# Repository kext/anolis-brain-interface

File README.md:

# Anolis Brain Interface

This repository contains the hardware and software files for the Anolis Brain Interface.

## PCB

The source and production files for the flexible PCB are in the [`pcb`](pcb) directory.
See the [Readme there](pcb/README.md) for instructions to setup your work environment.

## Firmware

The firmware for the brain interface and the dongle is in the [`firmware`](firmware) directory.
There you can find more information how to compile, flash and run the firmware on your device.

## Licence

The source code and PCB design files are dual licenced under the [MIT](LICENCE-MIT) and [Apache 2.0](LICENCE-APACHE) licences.

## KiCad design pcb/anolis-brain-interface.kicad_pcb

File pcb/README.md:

# Anolis Brain Interface PCB

## Setup

To work on the project files you need the KiCad EDA software in version 7.

KiCad can be downloaded from the [KiCad website](https://www.kicad.org/).
Download the version for your operating system and follow the instructions.

## Releases

Released versions can be found in the [`releases`](releases) directory.

## Changelog

All notable changes to the PCB should be listed below.

### [0.1.0] - 2023-11-20
- First version

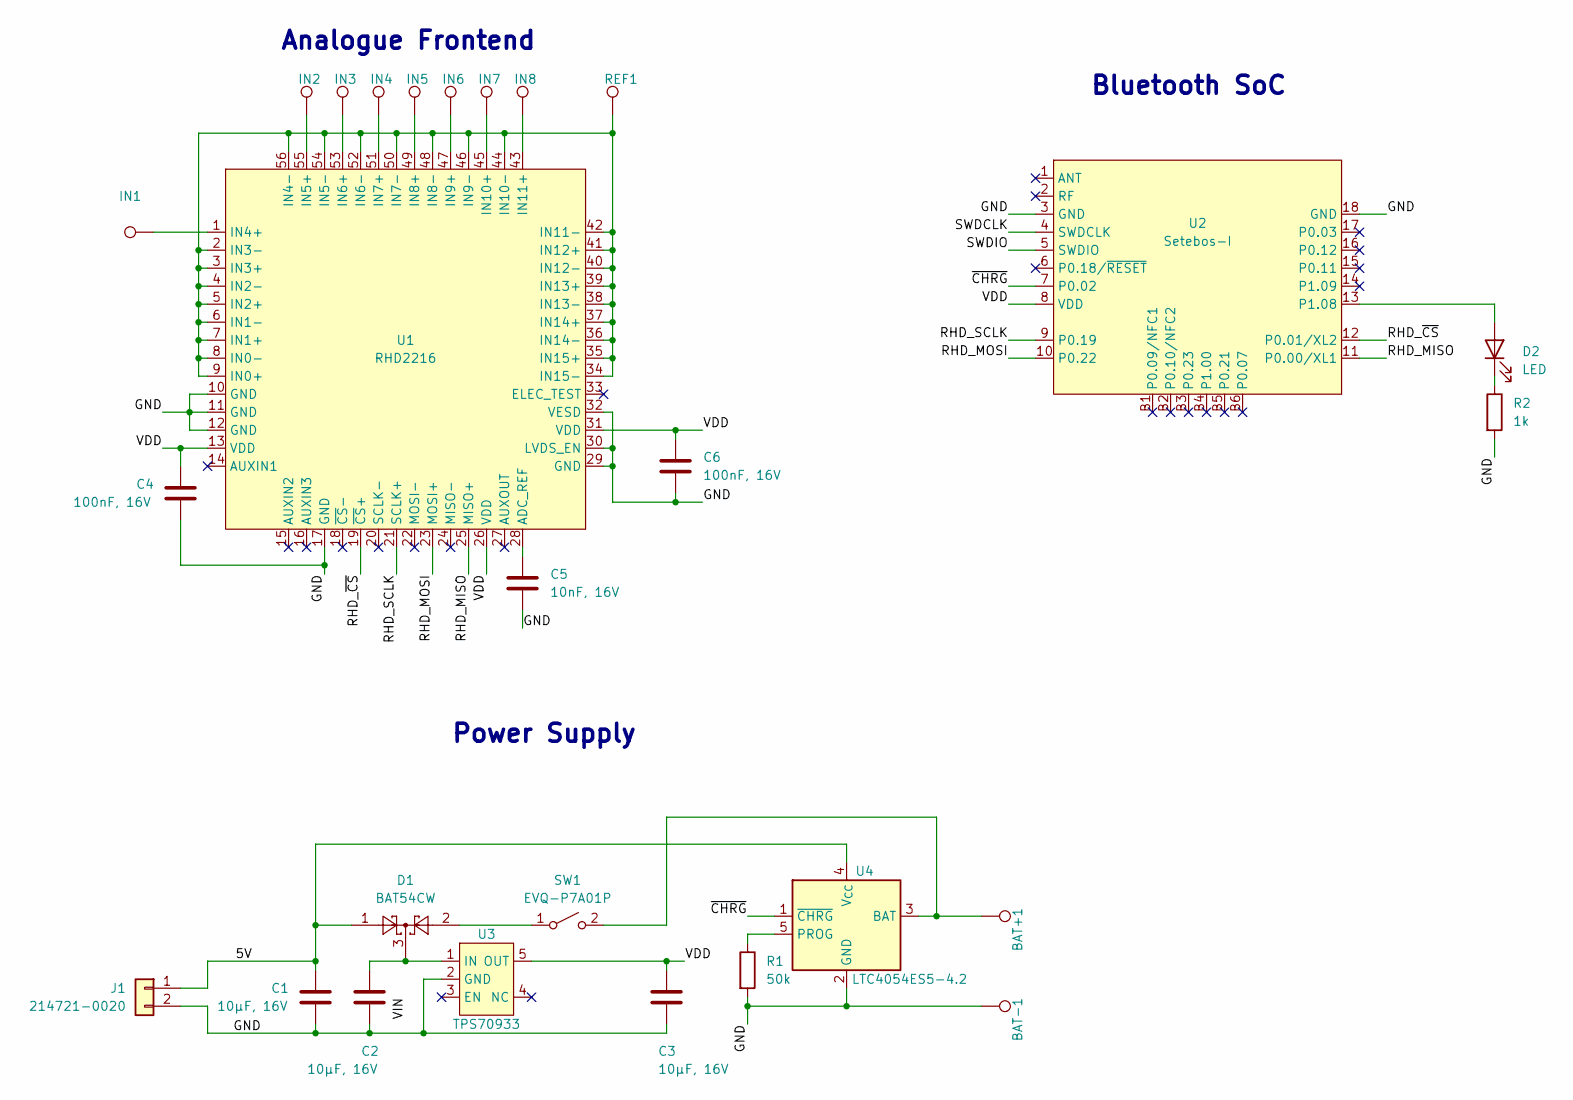
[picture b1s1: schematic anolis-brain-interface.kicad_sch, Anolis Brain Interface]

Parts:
BAT+1: TestPoint; TestPoint_Pad_1.0x1.0mm
BAT-1: TestPoint; TestPoint_Pad_1.0x1.0mm
C1, C2, C3: 10µF, 16V; C_0603_1608Metric
C4, C6: 100nF, 16V; C_0402_1005Metric
C5: 10nF, 16V; C_0402_1005Metric
D1: BAT54CW; SOT-323_SC-70
D2: LED; LED_0402_1005Metric
IN1, IN2, IN3, IN4, IN5, IN6, IN7, IN8: TestPoint; TestPoint_Pad_1.0x1.0mm
J1: 214721-0020
R1: 50k; R_0402_1005Metric
R2: 1k; R_0402_1005Metric
REF1: TestPoint; TestPoint_Pad_1.0x1.0mm
SW1: EVQ-P7A01P; SW_SPST_EVQP7A
U1: RHD2216; QFN-56-EP
U2: Setebos-I; setebos-no-drc
U3: TPS70933; TSOT-23-5
U4: LTC4054ES5-4.2; TSOT-23-5

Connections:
/5V: C1.1, D1.1, J1.1, U4.4 (V_{CC})
/GND: BAT-1.1, C1.2, C2.2, C3.2, C4.2, C5.2, C6.2, J1.2, R1.2, R2.2, U1.10 (GND), U1.11 (GND), U1.12 (GND), U1.17 (GND), U1.29 (GND), U1.30 (LVDS_EN), U1.32 (VESD), U2.3 (GND), U2.18 (GND), U3.2 (GND), U4.2 (GND)
/RHD_MISO: U1.25 (MISO+), U2.11 (P0.00/XL1)
/RHD_MOSI: U1.23 (MOSI+), U2.10 (P0.22)
/RHD_SCLK: U1.21 (SCLK+), U2.9 (P0.19)
/RHD_~CS: U1.19 (~CS+), U2.12 (P0.01/XL2)
/SWDCLK: U2.4 (SWDCLK)
/SWDIO: U2.5 (SWDIO)
/VDD: C3.1, C4.1, C6.1, U1.13 (VDD), U1.26 (VDD), U1.31 (VDD), U2.8 (VDD), U3.5 (OUT)
/~CHRG: U2.7 (P0.02), U4.1 (~CHRG)
unnamed: D2.2 (A), U2.13 (P1.08)
unnamed: D2.1 (K), R2.1
unnamed: D1.2, SW1.1 (A)
unnamed: BAT+1.1, SW1.2 (B), U4.3 (BAT)
unnamed: C5.1, U1.28 (ADC_REF)
unnamed: REF1.1, U1.2 (IN3-), U1.3 (IN3+), U1.4 (IN2-), U1.5 (IN2+), U1.6 (IN1-), U1.7 (IN1+), U1.8 (IN0-), U1.9 (IN0+), U1.34 (IN15-), U1.35 (IN15+), U1.36 (IN14-), U1.37 (IN14+), U1.38 (IN13-), U1.39 (IN13+), U1.40 (IN12-), U1.41 (IN12+), U1.42 (IN11-), U1.44 (IN10-), U1.46 (IN9-), U1.48 (IN8-), U1.50 (IN7-), U1.52 (IN6-), U1.54 (IN5-), U1.56 (IN4-)
unnamed: IN1.1, U1.1 (IN4+)
unnamed: IN2.1, U1.55 (IN5+)
unnamed: IN3.1, U1.53 (IN6+)
unnamed: IN4.1, U1.51 (IN7+)
unnamed: IN5.1, U1.49 (IN8+)
unnamed: IN6.1, U1.47 (IN9+)
unnamed: IN7.1, U1.45 (IN10+)
unnamed: IN8.1, U1.43 (IN11+)
unnamed: C2.1, D1.3, U3.1 (IN)
unnamed: R1.1, U4.5 (PROG)

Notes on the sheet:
Power Supply
Analogue Frontend
Bluetooth SoC

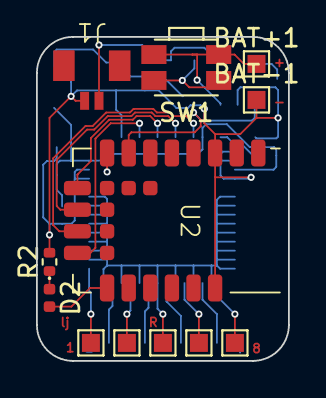
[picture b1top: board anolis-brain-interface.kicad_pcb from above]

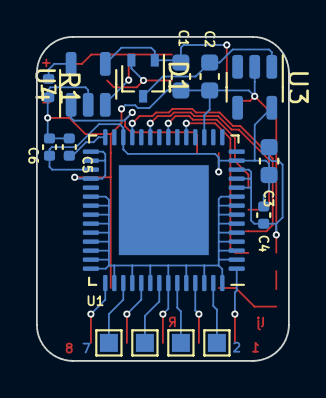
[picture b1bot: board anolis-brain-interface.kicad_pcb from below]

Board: 2 copper layers, 14.0 x 18.0 mm, 27 parts (15 on the bottom side), 24 nets.

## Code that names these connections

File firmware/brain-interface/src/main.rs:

//! Firmware for the Anolis Brain Interface

#![no_std]
#![no_main]
#![feature(type_alias_impl_trait)]

extern crate alloc;

use core::{cell::RefCell, ops::BitAnd};

use data_channel::{BoxPacket, L2capError};
use defmt::{info, unwrap, warn};
use embassy_executor::Spawner;
use embassy_futures::join::join;
use embassy_nrf::{
    bind_interrupts,
    gpio::{AnyPin, Input, Level, Output, OutputDrive, Pull},
    interrupt, peripherals,
    uarte::{self, UarteTx},
};
use embassy_time::Timer;
use embedded_alloc::Heap;
use nrf_softdevice::{
    ble::{
        l2cap::{self, L2cap, Packet, RxError},
        peripheral::{self, ConnectableAdvertisement},
        Phy, TxPower,
    },
    raw, Softdevice,
};

// global logger
use defmt_rtt as _;
// time driver
use embassy_nrf as _;
use panic_probe as _;

mod rhd2216;
use rhd2216::RHD2216;

/// Use the embedded alloc heap to enable [`Vec`](alloc::vec::Vec) and [`BoxPacket`].
#[global_allocator]
static HEAP: Heap = Heap::empty();

bind_interrupts!(struct Irqs {
    TIMER2 => rhd2216::InterruptHandler;
    UARTE1 => uarte::InterruptHandler<peripherals::UARTE1>;
});

/// The Softdevice task. Must be started after enabling the Softdevice.
#[embassy_executor::task]
async fn softdevice_task(sd: &'static Softdevice) -> ! {
    sd.run().await
}

#[embassy_executor::task]
async fn blink_task(led_pin: AnyPin, chrg_pin: AnyPin) -> ! {
    let mut led = Output::new(led_pin, Level::Low, OutputDrive::Standard);
    let chrg_status = Input::new(chrg_pin, Pull::Up);
    loop {
        for i in 0..4 {
            led.set_level(Level::from(i.bitand(1) == 0 || chrg_status.is_high()));
            Timer::after_millis(500).await;
        }
    }
}

/// Advertisement data for the device.
/// Contains the UUID of the brain interface service so the dongle knows to which device to connect.
#[rustfmt::skip]
const ADVERTISEMENT_DATA: &[u8] = &[
    // Flags
    2, 1, raw::BLE_GAP_ADV_FLAGS_LE_ONLY_GENERAL_DISC_MODE as u8,
    // Complete List of 128-bit Service Class UUIDs
    // edb74b42-8347-4285-a102-86f0b64c533c
    17, 7,
    0x3c, 0x53, 0x4c, 0xb6, 0xf0, 0x86, 0x02, 0xa1,
    0x85, 0x42, 0x47, 0x83, 0x42, 0x4b, 0xb7, 0xed,
];

/// Get the [`ConnectableAdvertisement`] for this device.
pub fn advertisement() -> ConnectableAdvertisement<'static> {
    ConnectableAdvertisement::ScannableUndirected {
        adv_data: ADVERTISEMENT_DATA,
        scan_data: &[],
    }
}

/// Alias for the packet type to have one place to change the size.
type MyPacket = BoxPacket<2048>;

/// Shared state between the receiver and sender task.
#[derive(defmt::Format)]
struct State {
    should_stop: bool,
}

/// Start the RHD and keep sending data packets over the L2CAP channel.
async fn send_rhd_data(
    rhd: &mut RHD2216<'_>,
    channel: &l2cap::Channel<MyPacket>,
    state: &RefCell<State>,
) -> Result<(), L2capError<MyPacket>> {
    info!("Starting");
    let mut rhd = rhd.start();
    loop {
        if state.borrow().should_stop {
            return Ok(());
        }
        let d = rhd.read().await;
        let mut packet = MyPacket::new().ok_or(RxError::AllocateFailed)?;
        assert!(MyPacket::MTU / 2 > d.frames.len());
        packet.append(&[(d.sequence_number & 255) as u8, d.channels as u8]);
        for v in &d.frames {
            packet.append(&v.to_le_bytes());
        }
        channel.try_tx(packet).or_else(|e| {
            if let l2cap::TxError::TxQueueFull(_) = e {
                warn!("Packet lost");
                Ok(())
            } else {
                Err(e)
            }
        })?;
    }
}

/// Receive commands and interpret them.
async fn receive_commands(channel: &l2cap::Channel<MyPacket>, state: &RefCell<State>) -> () {
    if let Ok(_) = channel.rx().await {
        state.borrow_mut().should_stop = true;
    }
}

/// The main task.
#[embassy_executor::main]
async fn main(spawner: Spawner) {
    info!("Start");

    // Initialise allocator
    {
        use core::mem::MaybeUninit;
        const HEAP_SIZE: usize = 1024 * 128;
        static mut HEAP_MEM: [MaybeUninit<u8>; HEAP_SIZE] = [MaybeUninit::uninit(); HEAP_SIZE];
        unsafe { HEAP.init(HEAP_MEM.as_ptr() as usize, HEAP_SIZE) }
    }

    // First we get the peripherals access crate.
    let mut config = embassy_nrf::config::Config::default();
    config.gpiote_interrupt_priority = interrupt::Priority::P3;
    config.time_interrupt_priority = interrupt::Priority::P3;
    let p = embassy_nrf::init(config);

    let config = nrf_softdevice::Config {
        clock: Some(raw::nrf_clock_lf_cfg_t {
            source: raw::NRF_CLOCK_LF_SRC_SYNTH as u8,
            rc_ctiv: 0,
            rc_temp_ctiv: 0,
            accuracy: raw::NRF_CLOCK_LF_ACCURACY_500_PPM as u8,
        }),
        conn_gap: Some(raw::ble_gap_conn_cfg_t {
            conn_count: 1,
            event_length: 40,
        }),
        conn_gatt: Some(raw::ble_gatt_conn_cfg_t { att_mtu: 256 }),
        conn_gattc: Some(raw::ble_gattc_conn_cfg_t {
            write_cmd_tx_queue_size: 0,
        }),
        conn_gatts: Some(raw::ble_gatts_conn_cfg_t {
            hvn_tx_queue_size: 0,
        }),
        gatts_attr_tab_size: Some(raw::ble_gatts_cfg_attr_tab_size_t {
            attr_tab_size: 1024,
        }),
        gap_role_count: Some(raw::ble_gap_cfg_role_count_t {
            adv_set_count: 1,
            periph_role_count: 1,
            central_role_count: 1,
            central_sec_count: 0,
            _bitfield_1: raw::ble_gap_cfg_role_count_t::new_bitfield_1(0),
        }),
        gap_device_name: Some(raw::ble_gap_cfg_device_name_t {
            p_value: b"Brain Interface" as *const u8 as _,
            current_len: 15,
            max_len: 15,
            write_perm: raw::ble_gap_conn_sec_mode_t {
                _bitfield_1: raw::ble_gap_conn_sec_mode_t::new_bitfield_1(1, 1),
            },
            _bitfield_1: raw::ble_gap_cfg_device_name_t::new_bitfield_1(
                raw::BLE_GATTS_VLOC_STACK as u8,
            ),
        }),
        conn_l2cap: Some(raw::ble_l2cap_conn_cfg_t {
            ch_count: 1,
            rx_mps: 256,
            tx_mps: 256,
            rx_queue_size: 3,
            tx_queue_size: data_channel::QUEUE_SIZE,
        }),
        ..Default::default()
    };

    // Pin definitions
    let _b1: AnyPin = p.P0_09.into();
    let _b2: AnyPin = p.P0_10.into();
    let _b3: AnyPin = p.P0_23.into();
    let _b4: AnyPin = p.P1_00.into();
    let _b5: AnyPin = p.P0_21.into();
    let _b6: AnyPin = p.P0_07.into();

    let _chrg: AnyPin = p.P0_02.into();

    let _led: AnyPin = p.P1_08.into();

    let _rhd_cs: AnyPin = p.P0_01.into();
    let _rhd_clk: AnyPin = p.P0_19.into();
    let _rhd_mosi: AnyPin = p.P0_22.into();
    let _rhd_miso: AnyPin = p.P0_00.into();

    let sd = Softdevice::enable(&config);
    let l2cap = L2cap::init(sd);

    unwrap!(spawner.spawn(softdevice_task(sd)));
    unwrap!(spawner.spawn(blink_task(_led, _chrg)));

    // Enable UARTE, otherwise SPI3 will not work.
    let mut uart = UarteTx::new(p.UARTE1, Irqs, _b1, Default::default());
    let _ = uart.write(&[1, 2, 3]).await;

    let mut rhd = RHD2216::new(
        Irqs,
        p.SPI3,
        p.TIMER1,
        p.TIMER2,
        p.PPI_CH0.into(),
        p.PPI_CH1.into(),
        _rhd_cs,
        _rhd_clk,
        _rhd_mosi,
        _rhd_miso,
    );

    loop {
        info!("Waiting for connection");
        let config = peripheral::Config {
            tx_power: TxPower::Plus8dBm,
            secondary_phy: Phy::M2,
            interval: 160,
            ..Default::default()
        };

        if let Ok(connection) =
            peripheral::advertise_connectable(sd, advertisement(), &config).await
        {
            info!("advertising done! I have a connection.");
            let config = nrf_softdevice::ble::l2cap::Config { credits: 3 };
            let channel = l2cap.listen(&connection, &config, data_channel::PSM).await;
            if let Ok(channel) = channel {
                let state = RefCell::new(State { should_stop: false });
                let _result = join(
                    send_rhd_data(&mut rhd, &channel, &state),
                    receive_commands(&channel, &state),
                )
                .await;
                info!("{}", _result);
            }
        }
        Timer::after_millis(1000).await;
    }
}

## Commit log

2023-10-17 First commit.
2023-10-17 Added links.
2023-10-17 Started work on PCB.
2023-10-17 Added uSD socket.
2023-10-18 Added power supply.
2023-10-18 Added capacitors.
2023-10-18 Added attachment slits.
2023-10-18 Created doc folder and list of questions.
2023-10-18 Changed board material to polyimide.
2023-10-18 Added battery connector.
2023-10-19 Added question about lizard species.
2023-10-19 Diode added.
2023-10-25 First draft for the firmware.
2023-10-25 Documentation for the RHD2216.
2023-10-25 Settings for Rust Analyzer.
2023-10-25 Fill the TX buffer with the correct commands.
2023-10-25 Don't forget the samples in the first overflow.
2023-10-26 Enable debug info for release mode.
2023-10-26 RHD works.
2023-10-27 Implemented BLE liveview.
2023-10-27 Throughput calculations.
2023-10-27 Added words for spell checker.
2023-10-27 Answers.
2023-10-27 Tuned parameters.
2023-10-27 Questions updated.
2023-10-30 Improved code.
2023-10-30 Segmented draft.
2023-11-01 Improved formatting.
2023-11-01 Clippy improvements.
2023-11-01 Added counter.
2023-11-03 Created a Cargo workspace for the firmware.
2023-11-03 More words for the spell checker.
2023-11-03 Power supply documentation.
2023-11-03 Removed dependencies.
2023-11-05 Created BLE Service library.
2023-11-06 Dongle WIP.
2023-11-06 Rewrote transport layer using L2CAP.
2023-11-08 Implemented browser display with WebUSB.
2023-11-08 Updated dependencies.
2023-11-09 Report 2023-11-09.
2023-11-09 We need to start UARTE at the beginning or SPI will not work.
2023-11-10 Measured power consumption.
2023-11-10 Added SKIP_CHANNELS.
2023-11-10 A picture of the estimated board dimensions.
2023-11-11 Implemented Clippy suggestions.
2023-11-14 Made allocation failure for packet explicit.
2023-11-14 More documentation.
2023-11-14 Better names.
2023-11-14 Measured component weights.
2023-11-15 Better docs.
2023-11-15 Stray backtick.
2023-11-17 New PCB design.
2023-11-18 Implemented a run token for RHD.
2023-11-20 PCB done.
2023-11-20 Improved routing.
2023-11-20 PCB version 0.1.0.
2023-11-20 Order number corrected.
2023-11-20 Fixed inconsistent routing.
2023-11-21 Include sequence counter in the RHD module.
2023-11-21 Less confusing terminology.
2023-11-28 Replaced incorrect order number.
2023-12-01 Fixed reconnection problems and improved interface.
2023-12-01 Better plots.
2023-12-05 Automatically format rust files.
2023-12-07 Adapted the code for the final hardware.
2023-12-08 Unified data and command channels.
2023-12-08 Licences.
2023-12-08 Added instructions for flashing the softdevice.
2023-12-14 Made connection more stable.
2023-12-18 Implemented data save function.
2023-12-25 Format.
2024-01-11 More comments.
2024-01-11 Data to CSV script.
2024-01-11 Readme for frontend.
